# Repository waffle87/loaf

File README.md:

<div align="center">
  <h1>loaf</h1>
  <h4>A Minivan compatible PCB built with through hole components</h4>

</div>

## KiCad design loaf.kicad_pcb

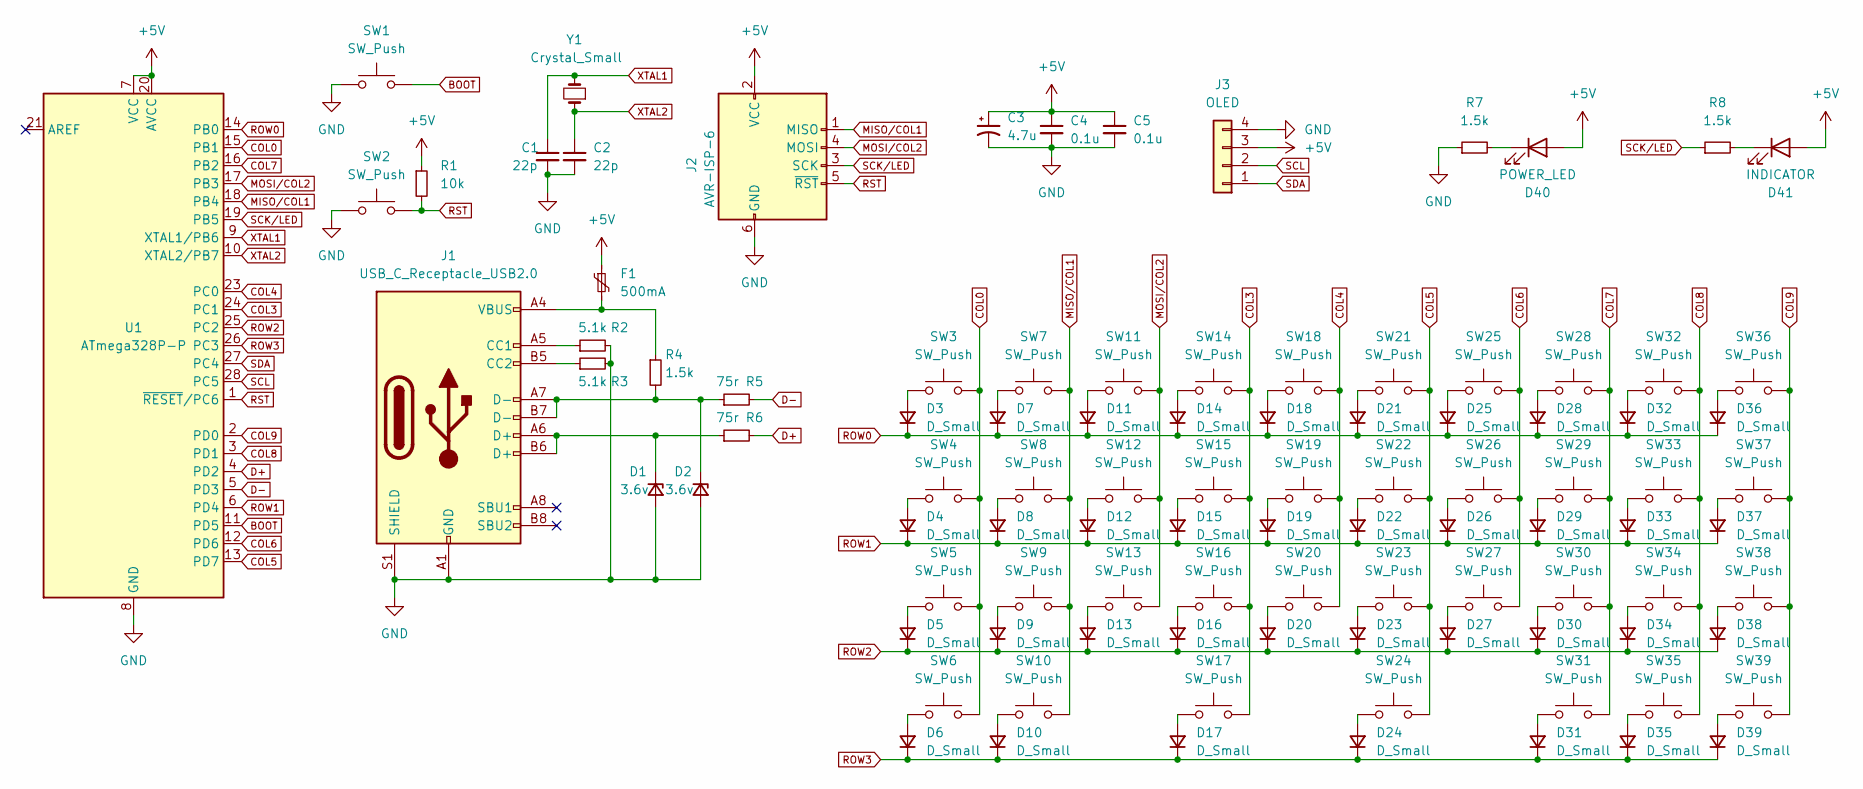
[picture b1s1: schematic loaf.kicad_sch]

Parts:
C1, C2: 22p; C_Disc_D3.0mm_W1.6mm_P2.50mm
C3: 4.7u; CP_Radial_D4.0mm_P1.50mm
C4, C5: 0.1u; C_Disc_D4.3mm_W1.9mm_P5.00mm
D1, D2: 3.6v; D_DO-35_SOD27_P5.08mm_Vertical_AnodeUp
D3, D4, D5, D6, D7, D8, D9, D10, D11, D12, D13, D14, D15, D16, D17, D18, D19, D20, D21, D22, D23, D24, D25, D26, D27, D28, D29, D30, D31, D32, D33, D34, D35, D36, D37, D38, D39: D_Small; D_SOD-123
D40: POWER_LED; LED_D3.0mm
D41: INDICATOR; LED_D3.0mm
F1: 500mA; polyfuse_5.1mm
J1: USB_C_Receptacle_USB2.0; USB_C_GCT_USB4085
J2: AVR-ISP-6; PinHeader_2x03_P2.54mm_Vertical
J3: OLED; OLED_v2
R1: 10k; R_Axial_DIN0204_L3.6mm_D1.6mm_P5.08mm_Horizontal
R2, R3: 5.1k; R_Axial_DIN0204_L3.6mm_D1.6mm_P5.08mm_Horizontal
R4, R7, R8: 1.5k; R_Axial_DIN0204_L3.6mm_D1.6mm_P5.08mm_Horizontal
R5, R6: 75r; R_Axial_DIN0204_L3.6mm_D1.6mm_P5.08mm_Horizontal
SW1, SW2: SW_Push; SW_PUSH_6mm
SW3, SW7, SW8, SW9, SW11, SW12, SW13, SW14, SW15, SW16, SW18, SW19, SW20, SW21, SW22, SW23, SW25, SW26, SW27, SW28, SW29, SW30, SW31, SW32, SW33, SW34, SW35, SW38, SW39: SW_Push; MXOnly-1U-NoLED
SW4, SW6: SW_Push; MXOnly-1.25U-NoLED
SW5, SW36: SW_Push; MXOnly-1.75U-NoLED
SW10, SW37: SW_Push; MXOnly-1.5U-NoLED
SW17: SW_Push; MXOnly-2.75U-ReversedStabilizers-NoLED
SW24: SW_Push; MXOnly-2.25U-ReversedStabilizers-NoLED
U1: ATmega328P-P; DIP-28_W7.62mm
Y1: Crystal_Small; Crystal_HC49-4H_Vertical

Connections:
+5V: C3.1, C4.1, C5.1, D40.2 (A), D41.2 (A), F1.1, J2.2 (VCC), J3.3, R1.1, U1.7 (VCC), U1.20 (AVCC)
BOOT: SW1.2, U1.11 (PD5)
COL0: SW3.2, SW4.2, SW5.2, SW6.2, U1.15 (PB1)
COL3: SW14.2, SW15.2, SW16.2, SW17.2, U1.24 (PC1)
COL4: SW18.2, SW19.2, SW20.2, U1.23 (PC0)
COL5: SW21.2, SW22.2, SW23.2, SW24.2, U1.13 (PD7)
COL6: SW25.2, SW26.2, SW27.2, U1.12 (PD6)
COL7: SW28.2, SW29.2, SW30.2, SW31.2, U1.16 (PB2)
COL8: SW32.2, SW33.2, SW34.2, SW35.2, U1.3 (PD1)
COL9: SW36.2, SW37.2, SW38.2, SW39.2, U1.2 (PD0)
D+: R6.2, U1.4 (PD2)
D-: R5.2, U1.5 (PD3)
GND: C1.2, C2.2, C3.2, C4.2, C5.2, D1.2 (A), D2.2 (A), J1.A1 (GND), J1.A12 (GND), J1.B1 (GND), J1.B12 (GND), J1.S1 (SHIELD), J2.6 (GND), J3.4, R2.2, R3.2, R7.1, SW1.1, SW2.1, U1.8 (GND), U1.22 (GND)
MISO/COL1: J2.1 (MISO), SW7.2, SW8.2, SW9.2, SW10.2, U1.18 (PB4)
MOSI/COL2: J2.4 (MOSI), SW11.2, SW12.2, SW13.2, U1.17 (PB3)
unnamed: D1.1 (K), J1.A6 (D+), J1.B6 (D+), R6.1
unnamed: D2.1 (K), J1.A7 (D-), J1.B7 (D-), R4.2, R5.1
unnamed: D3.2 (A), SW3.1
unnamed: D4.2 (A), SW4.1
unnamed: D5.2 (A), SW5.1
unnamed: D6.2 (A), SW6.1
unnamed: D7.2 (A), SW7.1
unnamed: D8.2 (A), SW8.1
unnamed: D9.2 (A), SW9.1
unnamed: D10.2 (A), SW10.1
unnamed: D11.2 (A), SW11.1
unnamed: D12.2 (A), SW12.1
unnamed: D13.2 (A), SW13.1
unnamed: D14.2 (A), SW14.1
unnamed: D15.2 (A), SW15.1
unnamed: D16.2 (A), SW16.1
unnamed: D17.2 (A), SW17.1
unnamed: D18.2 (A), SW18.1
unnamed: D19.2 (A), SW19.1
unnamed: D20.2 (A), SW20.1
unnamed: D21.2 (A), SW21.1
unnamed: D22.2 (A), SW22.1
unnamed: D23.2 (A), SW23.1
unnamed: D24.2 (A), SW24.1
unnamed: D25.2 (A), SW25.1
unnamed: D26.2 (A), SW26.1
unnamed: D27.2 (A), SW27.1
unnamed: D28.2 (A), SW28.1
unnamed: D29.2 (A), SW29.1
unnamed: D30.2 (A), SW30.1
unnamed: D31.2 (A), SW31.1
unnamed: D32.2 (A), SW32.1
unnamed: D33.2 (A), SW33.1
unnamed: D34.2 (A), SW34.1
unnamed: D35.2 (A), SW35.1
unnamed: D36.2 (A), SW36.1
unnamed: D37.2 (A), SW37.1
unnamed: D38.2 (A), SW38.1
unnamed: D39.2 (A), SW39.1
unnamed: D40.1 (K), R7.2
unnamed: D41.1 (K), R8.2
unnamed: F1.2, J1.A4 (VBUS), J1.A9 (VBUS), J1.B4 (VBUS), J1.B9 (VBUS), R4.1
unnamed: J1.A5 (CC1), R2.1
unnamed: J1.B5 (CC2), R3.1
ROW0: D3.1 (K), D7.1 (K), D11.1 (K), D14.1 (K), D18.1 (K), D21.1 (K), D25.1 (K), D28.1 (K), D32.1 (K), D36.1 (K), U1.14 (PB0)
ROW1: D4.1 (K), D8.1 (K), D12.1 (K), D15.1 (K), D19.1 (K), D22.1 (K), D26.1 (K), D29.1 (K), D33.1 (K), D37.1 (K), U1.6 (PD4)
ROW2: D5.1 (K), D9.1 (K), D13.1 (K), D16.1 (K), D20.1 (K), D23.1 (K), D27.1 (K), D30.1 (K), D34.1 (K), D38.1 (K), U1.25 (PC2)
ROW3: D6.1 (K), D10.1 (K), D17.1 (K), D24.1 (K), D31.1 (K), D35.1 (K), D39.1 (K), U1.26 (PC3)
RST: J2.5 (~RST), R1.2, SW2.2, U1.1 (~RESET/PC6)
SCK/LED: J2.3 (SCK), R8.1, U1.19 (PB5)
SCL: J3.2, U1.28 (PC5)
SDA: J3.1, U1.27 (PC4)
XTAL1: C1.1, U1.9 (XTAL1/PB6), Y1.2
XTAL2: C2.1, U1.10 (XTAL2/PB7), Y1.1

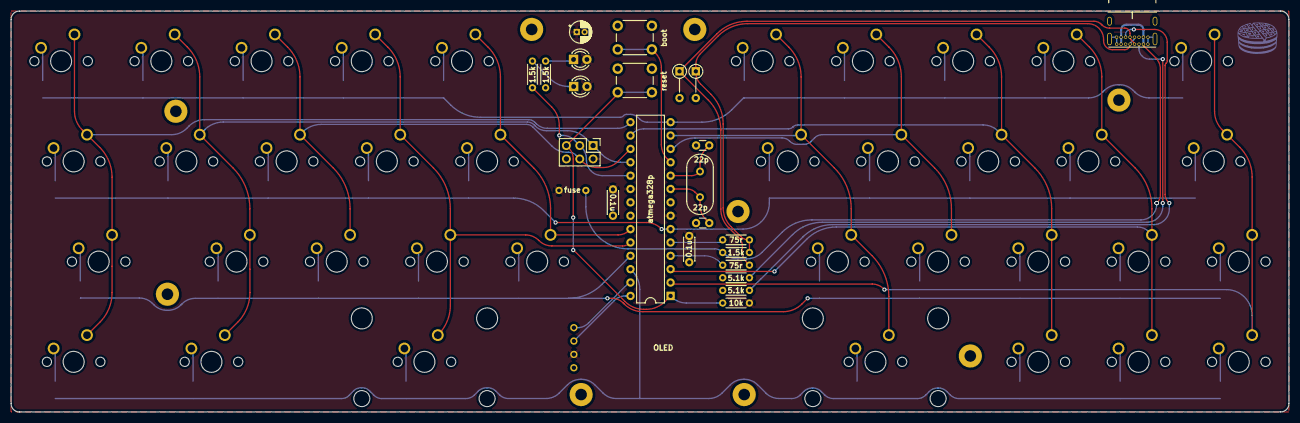
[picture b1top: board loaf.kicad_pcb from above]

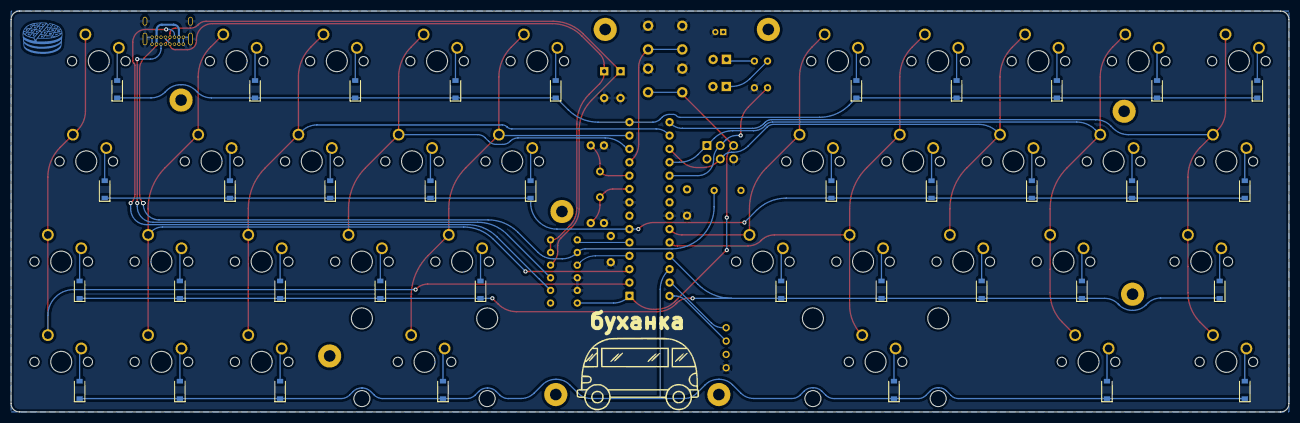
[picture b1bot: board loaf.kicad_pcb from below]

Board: 2 copper layers, 242.9 x 76.2 mm, 99 parts (37 on the bottom side), 69 nets.

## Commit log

2022-01-12 add submodules
2022-01-12 readme updates
2022-01-12 add cover mounting points
2022-01-12 fix stray trace
2022-01-12 switch diodes to sod-123
2022-01-13 add bom
